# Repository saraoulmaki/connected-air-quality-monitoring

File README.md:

# Connected Air Quality Monitoring System

**Embedded air quality monitoring system integrating STM32 microcontrollers, wireless communication, MQTT, Qt/C++, SQLite, and custom PCB design.**

Academic project developed during the 2024–2025 academic year as part of the *Bachelor Universitaire de Technologie (BUT) in Electrical Engineering and Industrial Computing (GEII)* at IUT Montpellier, France.

## Project Overview

This project explores the design and development of a distributed air quality monitoring system, combining embedded electronics, wireless sensor communication, data processing, and desktop software.

The system was designed around several interconnected components:

- A custom sensor node PCB integrating an STM32G030 microcontroller and environmental sensors.
- An nRF24L01 wireless communication interface.
- An STM32-based gateway for receiving sensor data and forwarding information over a network using MQTT.
- A Qt/C++ application for serial data acquisition, AES decryption, and SQLite storage.
- A Qt graphical application for configuring the wireless communication system.

The project was developed across two academic semesters (S5 and S6), with different software and communication architectures explored throughout its development.

## System Architecture

The system combines embedded data acquisition, wireless communication, and software-based data processing.

### Sensor Node

The sensor node is based on a custom PCB designed using KiCad.

Its main components include:

- **STM32G030K8** microcontroller
- **ENS160** air quality sensor
- **AHT21** temperature and humidity sensor
- **nRF24L01** wireless transceiver
- Power supply and voltage regulation circuitry
- Programming and communication connectors

The STM32 communicates with the environmental sensors and provides the embedded processing capabilities required for data acquisition.

The nRF24L01 interface enables wireless communication with other parts of the system.

### STM32 Gateway

The gateway firmware targets the **STM32F439ZI** microcontroller and was developed using STM32CubeIDE.

Its architecture incorporates:

- **FreeRTOS** for task management
- **lwIP** for network communication
- **MQTT** for message transmission
- **SPI** communication with the nRF24L01 transceiver
- Custom application modules for wireless communication and MQTT handling

The gateway was intended to bridge wireless sensor communication with an IP-based network.

### Desktop Applications

Two Qt/C++ applications were developed during the project.

**Serial Data Receiver — Semester 5**

A console-based Qt application designed to receive data through a serial interface, process encrypted messages, and store information in an SQLite database.

Technologies and concepts:

- Qt Core and Qt Serial Port
- C/C++
- AES-128 decryption
- Serial communication
- SQLite database integration

**nRF24L01 Configurator — Semester 6**

A Qt Widgets graphical application developed to configure wireless communication parameters through a serial interface.

It includes functionality related to AES key configuration and communication with the connected embedded device.

Technologies and concepts:

- Qt Widgets
- Qt Designer
- Qt Serial Port
- C++17
- Serial communication and device configuration

## Hardware Design

The sensor node PCB was designed using **KiCad**, covering schematic capture, component placement, PCB routing, and 3D visualization.

The board integrates the microcontroller, sensor interfaces, wireless module connections, power circuitry, and programming interfaces.

### PCB Layout

### PCB Schematic

### 3D PCB Visualization

Additional hardware views and the original KiCad design files are available in the repository.

*Note: Some external modules do not have associated 3D models in the KiCad visualization.*

## Technologies Used

| Category | Technologies |
|---|---|
| Microcontrollers | STM32G030K8, STM32F439ZI |
| Programming | C, C++ |
| Embedded development | STM32CubeIDE, STM32CubeMX |
| Real-time systems | FreeRTOS |
| Wireless communication | nRF24L01, SPI |
| Networking | lwIP, MQTT |
| Desktop software | Qt, Qt Widgets, Qt Serial Port |
| Data processing | AES-128 |
| Database | SQLite |
| PCB design | KiCad |
| Development tools | Git, GitHub |

## Repository Structure

```text
connected-air-quality-monitoring/
├── hardware/
│   └── sensor-node-pcb/
│       ├── Capteur.kicad_pcb
│       ├── Capteur.kicad_sch
│       ├── Capteur.kicad_pro
│       └── Capteur.pdf
│
├── firmware/
│   └── s6-gateway-f439zi/
│       ├── Core/
│       ├── LWIP/
│       ├── userAppMqtt/
│       ├── userAppNrf/
│       ├── SAE_6_PASSERELLE.ioc
│       └── ...
│
├── software/
│   ├── s5-serial-to-sqlite/
│   │   ├── main.cpp
│   │   ├── serialportreader.cpp
│   │   ├── aes.c
│   │   ├── creaderasync.pro
│   │   └── ...
│   │
│   └── s6-nrf-configurator-gui/
│       ├── mainwindow.cpp
│       ├── mainwindow.ui
│       ├── serialportreader.cpp
│       ├── sae_6.pro
│       └── ...
│
├── docs/
│   └── images/
│
├── tools/
│   └── f303re-uart-led-test/
│
├── .gitignore
└── README.md
```

## My Contributions

This project was developed in a two-person team as part of my BUT GEII studies (2024–2025), in collaboration with **Cécile ALU**.

My contributions included:

- **PCB design and assembly:** Collaboratively designed the sensor node PCB using KiCad and personally soldered its electronic components.
- **Qt/C++ application development:** Independently developed the Qt applications for serial data acquisition, processing, and nRF24L01 configuration.
- **STM32 firmware development:** Worked alongside my project partner on embedded firmware development, with both of us contributing code and helping each other troubleshoot issues.
- **Hardware integration and testing:** Participated in debugging and testing, sharing the development hardware throughout the project.

The project combined individual software development with collaborative embedded systems engineering, from hardware design to firmware integration.

## Project Status and Limitations

**Status: Archived academic project (2024–2025).**

This repository preserves the available source files and design documents from the original project.

It is intended primarily as a technical portfolio and educational reference rather than a complete, ready-to-deploy system.

Important limitations include:

- Some original firmware components, including the STM32G030 sensor node firmware, are not available in this archive.
- The STM32F439ZI gateway source files are included, but certain external and third-party dependencies are not redistributed.
- The gateway may require additional libraries and project configuration before it can be compiled.
- Some modules reflect the original development state and may contain incomplete functionality or unresolved issues.
- Serial communication settings and application configuration may need to be adapted to the target hardware and operating system.
- The full end-to-end system has not been rebuilt or validated from the archived repository.

The source code is preserved to document the project's technical development rather than to represent a fully tested production implementation.

## Third-Party Components

The Qt serial receiver includes an AES implementation based on the open-source [tiny-AES-c](https://github.com/kokke/tiny-AES-c) project.

Its original public-domain dedication is included in:

`software/s5-serial-to-sqlite/UNLICENSE-tiny-AES-c.txt`

Additional third-party libraries used during the original embedded development are not necessarily included in this repository.

The presence of source code in this archive does not imply that all components were developed from scratch.

## Acknowledgements

Developed at **IUT Montpellier**, as part of the BUT GEII academic curriculum.

Special thanks to my project partner for the collaborative hardware and embedded firmware development.

---

**Sara OULMAKI**  
Embedded Systems & Electronics Engineering Student  
[GitHub](https://github.com/saraoulmaki)

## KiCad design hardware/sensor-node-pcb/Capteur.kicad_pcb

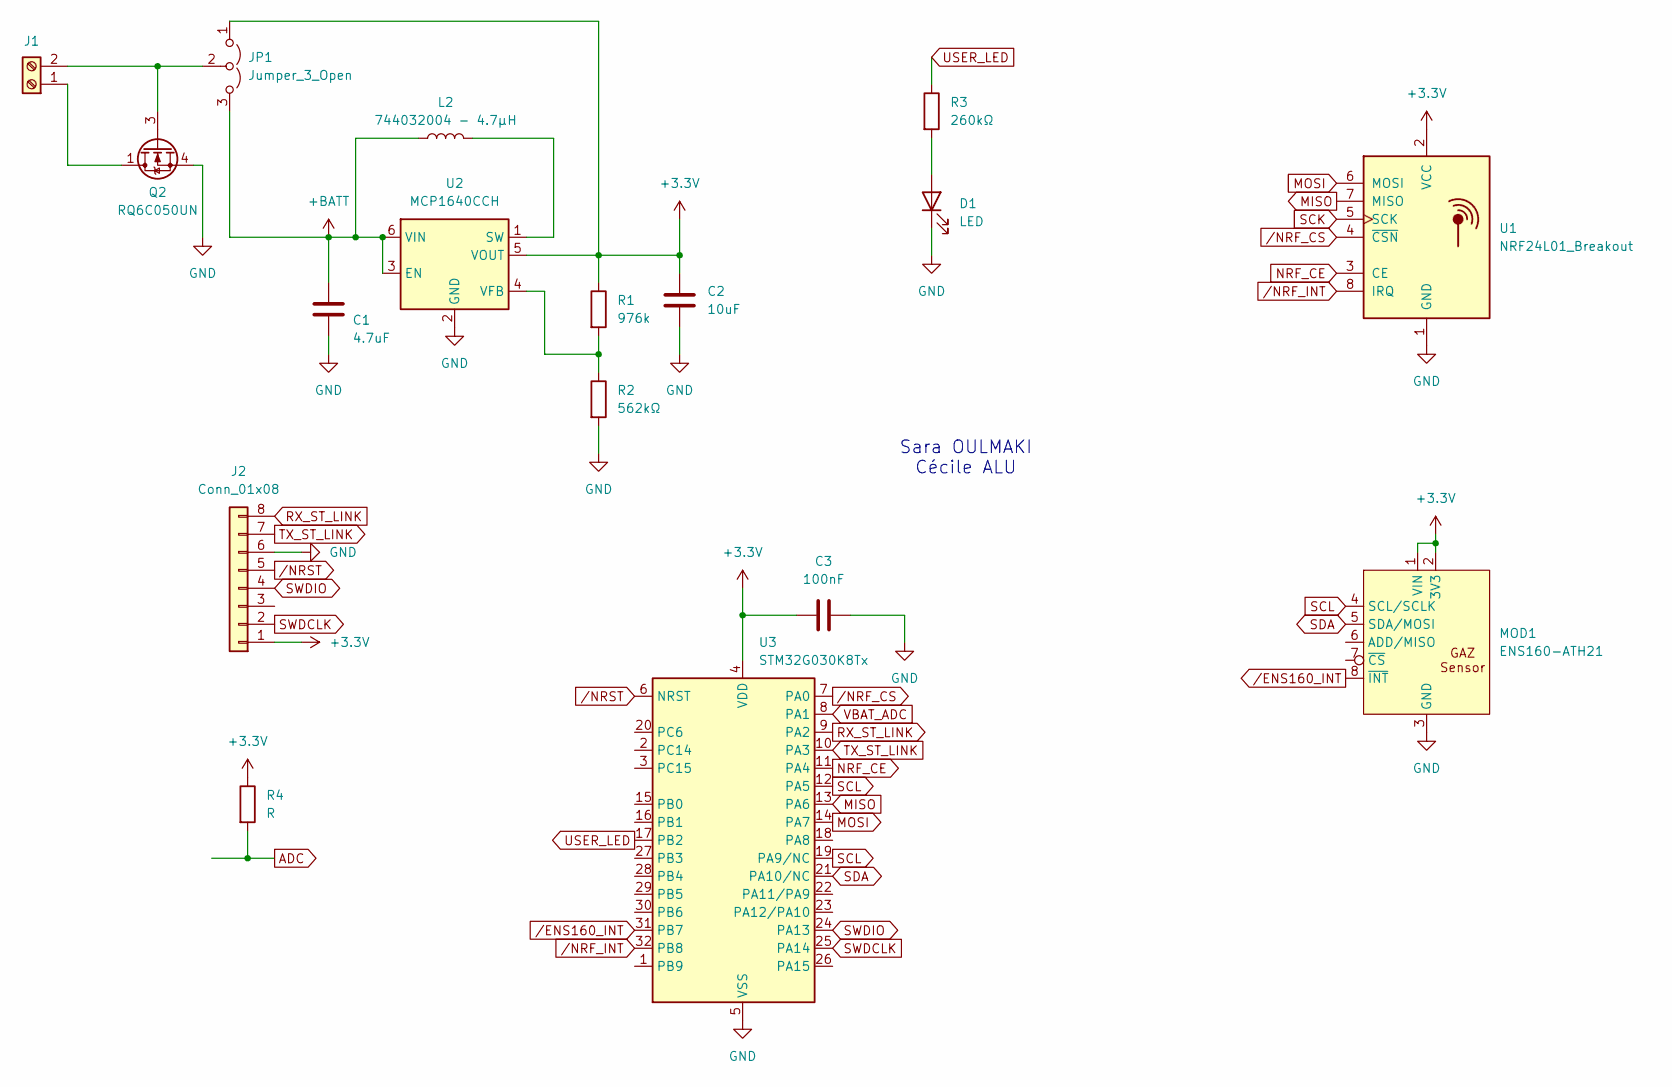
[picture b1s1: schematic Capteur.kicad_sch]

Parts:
C1: 4.7uF; C_0805_2012Metric_Pad1.18x1.45mm_HandSolder
C2: 10uF; C_0805_2012Metric_Pad1.18x1.45mm_HandSolder
C3: 100nF; C_0805_2012Metric_Pad1.18x1.45mm_HandSolder
D1: LED; LED_0805_2012Metric
J1: TerminalBlock_Phoenix_MPT-0,5-2-2.54_1x02_P2.54mm_Horizontal
J2: Conn_01x08; PinHeader_1x08_P2.54mm_Vertical
JP1: Jumper_3_Open; PinHeader_1x03_P2.54mm_Vertical
L2: 744032004 - 4.7µH; L_1210_3225Metric_Pad1.42x2.65mm_HandSolder
MOD1: ENS160-ATH21; ENS160-ATH21_Gaz_Sensor
Q2: RQ6C050UN; SOT-23-6_Handsoldering
R1: 976k; R_0805_2012Metric_Pad1.20x1.40mm_HandSolder
R2: 562kΩ; R_0805_2012Metric_Pad1.20x1.40mm_HandSolder
R3: 260kΩ; R_0805_2012Metric_Pad1.20x1.40mm_HandSolder
R4: R; R_0805_2012Metric_Pad1.20x1.40mm_HandSolder
U1: NRF24L01_Breakout; nRF24L01_Breakout
U2: MCP1640CCH; SOT-23-6
U3: STM32G030K8Tx; LQFP-32_7x7mm_P0.8mm

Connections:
+3.3V: C2.1, C3.1, J2.1, JP1.1 (A), MOD1.1 (VIN), MOD1.2 (3V3), R1.1, R4.1, U1.2 (VCC), U2.5 (VOUT), U3.4 (VDD)
+BATT: C1.1, JP1.3 (B), L2.1, U2.3 (EN), U2.6 (VIN); also elsewhere on the board
ADC: R4.2
GND: C1.2, C2.2, C3.2, D1.1 (K), J2.6, MOD1.3 (GND), Q2.4 (S), R2.2, U1.1 (GND), U2.2 (GND), U3.5 (VSS)
MISO: U1.7 (MISO), U3.13 (PA6)
MOSI: U1.6 (MOSI), U3.14 (PA7)
NRF_CE: U1.3 (CE), U3.11 (PA4)
unnamed: D1.2 (A), R3.2
unnamed: J1.1, Q2.1 (D), Q2.2 (D), Q2.5 (D), Q2.6 (D)
unnamed: J1.2, JP1.2 (C), Q2.3 (G)
unnamed 10: L2.2, U2.1 (SW); also elsewhere on the board
unnamed: R1.2, R2.1, U2.4 (VFB)
RX_ST_LINK: J2.8, U3.9 (PA2)
SCK: U1.5 (SCK)
SCL: MOD1.4 (SCL/SCLK), U3.12 (PA5), U3.19 (PA9/NC)
SDA: MOD1.5 (SDA/MOSI), U3.21 (PA10/NC)
SWDCLK: J2.2, U3.25 (PA14)
SWDIO: J2.4, U3.24 (PA13)
TX_ST_LINK: J2.7, U3.10 (PA3)
USER_LED: R3.1, U3.17 (PB2)
VBAT_ADC: U3.8 (PA1)
/ENS160_INT: MOD1.8 (~INT), U3.31 (PB7)
/NRF_CS: U1.4 (~CSN), U3.7 (PA0)
/NRF_INT: U1.8 (IRQ), U3.32 (PB8)
/NRST: J2.5, U3.6 (NRST)

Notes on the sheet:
Sara OULMAKI Cécile ALU

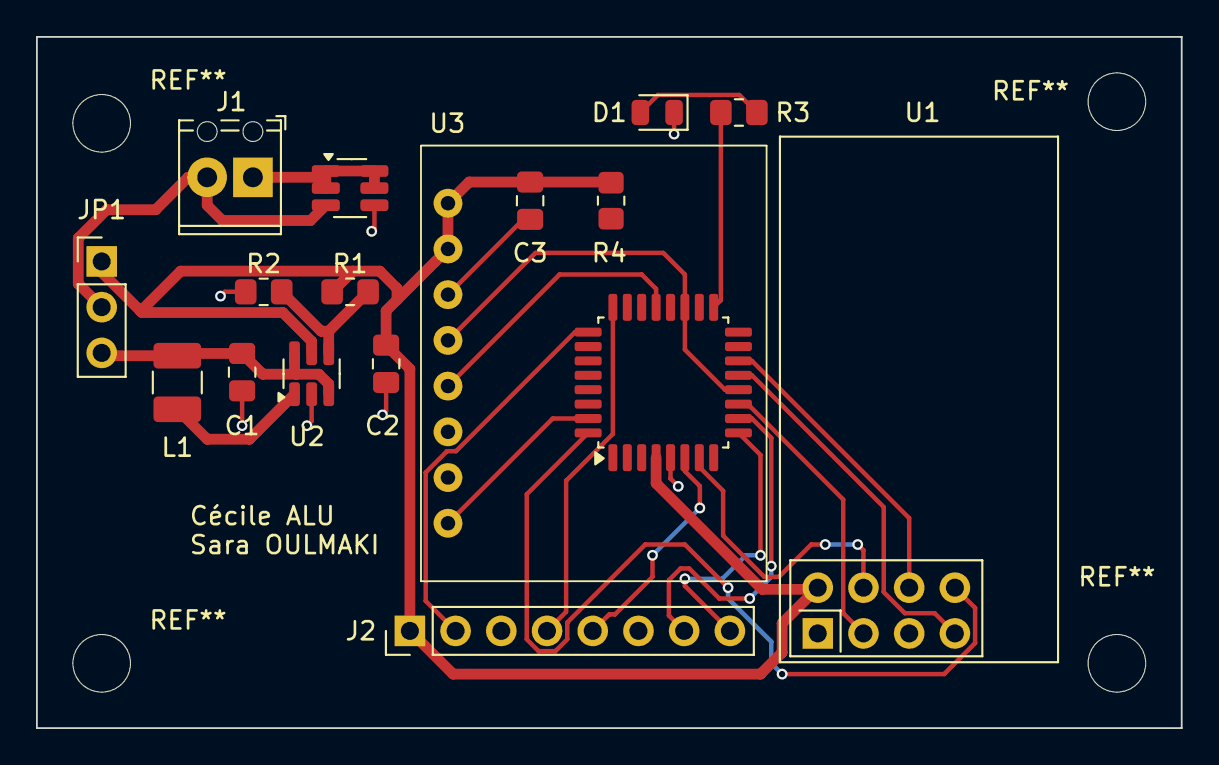
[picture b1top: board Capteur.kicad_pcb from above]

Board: 2 copper layers, 63.6 x 38.4 mm, 17 parts (0 on the bottom side), 22 nets.

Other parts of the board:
L1: 744032004 - 4.7µH; L_1210_3225Metric_Pad1.42x2.65mm_HandSolder

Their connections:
+BATT: L1.1; also elsewhere on the board
unnamed 10: L1.2; also elsewhere on the board
